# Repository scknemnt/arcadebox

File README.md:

# Arcade Box

Ev tipi ayakta kabin için **kiosk kabuk**. Windows veya Linux masaüstü görünmez: açılış → senin menün → oyun (RetroArch tam ekran) → menüye dönüş.

Bu depo **yazılımı** içerir. Ticari ROM, BIOS ve kutu görselleri **yok**. Kendi yasal dump’larını `roms/` ve `bios/` altına koyarsın.

**Hedef donanım:** Raspberry Pi 4 (8 GB) + HDMI (CRT/SCART sonra). Geliştirme: Windows.

---

## Ne yapar

- 4:3 CRT tarzı frontend (scanline, RGB mask, yıldız alanı)
- Klasör taraması: `roms/<sistem>/` içindeki her dosya menüde görünür
- Tek emülatör: **RetroArch** + libretro core
- Oyun çıkınca menü müziği ve liste geri gelir
- Servis menüsü: **F2** / logo (TEST, tuş ata, CRT)

Sistemler: Atari 2600, NES, SNES, Mega Drive, Arcade (FBNeo), Neo Geo, PlayStation.

---

## Bu repoda olmayanlar

| Klasör | Sen koyarsın |
|---|---|
| `roms/<sistem>/` | Yasal ROM / CHD / cue |
| `bios/psx/` | PS1 BIOS (`.bin`) |
| `roms/neogeo/neogeo.zip` | Neo Geo BIOS |
| `emulators/retroarch/` | Windows’ta portable RetroArch + `.dll` core |
| `music/` | İsteğe bağlı menü MP3 |

---

## Windows (geliştirme)

Python 3 (stdlib yeter). RetroArch portable:

```
emulators/retroarch/retroarch.exe
emulators/retroarch/cores/*.dll
```

| | |
|---|---|
| Pencere | `start.bat` |
| Tam ekran kiosk | `start-kiosk.bat` |
| Windows otostart | `kiosk/windows-otostart-kur.bat` bir kez |

Kabinde otomatik oturum aç (`netplwiz`). CRT için 800×600.

**Core’lar (Windows `.dll`):** Stella, Mesen (yedek Nestopia/FCEUmm), Snes9x, Genesis Plus GX, FBNeo, SwanStation (yedek Beetle PSX / PCSX ReARMed).

---

## Raspberry Pi 4 (kiosk)

- OS: **Raspberry Pi OS Lite 64-bit** (SD)
- Oyunlar: USB flash, klasör adı `ArcadeBox` (FAT32)
- Imager kullanıcı/hostname: `arcadebox`

USB’yi mavi USB3’e tak, SSH:

```sh
sudo mkdir -p /mnt/usb
sudo mount -t vfat /dev/sda1 /mnt/usb
cd /mnt/usb/ArcadeBox
tr -d '\r' < kiosk/pi-kur.sh > /tmp/pi-kur.sh
tr -d '\r' < kiosk/linux-start.sh > /tmp/linux-start.sh
sudo cp /tmp/linux-start.sh kiosk/linux-start.sh
sudo sh /tmp/pi-kur.sh
```

Windows satır sonları (`CRLF`) scripti bozar; `tr` ile LF yap. Script `ROOT=/` basarsa USB’den değil `/tmp` üzerinden çalışıyorsundur — normal. Autostart’ı README’deki Pi notlarına göre `~/.xinitrc` ile düzelt.

Core’lar (Linux `.so`, Windows DLL değil):

```sh
sudo apt-get install -y unzip wget
mkdir -p ~/.config/retroarch/cores
cd /tmp
for c in stella_libretro nestopia_libretro fceumm_libretro snes9x_libretro genesis_plus_gx_libretro fbneo_libretro pcsx_rearmed_libretro; do
  wget -O "$c.so.zip" "https://buildbot.libretro.com/nightly/linux/aarch64/latest/${c}.so.zip"
  unzip -o "$c.so.zip" -d ~/.config/retroarch/cores
done
```

veya `sh kiosk/pi-cores.sh`.

USB etiketi `ESD-USB` ise her açılışta `/mnt/arcade` bağlanır (`pi-kur.sh` fstab yazar). HDMI: güç soketine en yakın port.

---

## Klasörler

```
ArcadeBox/
  backend/arcadebox.py    yerel sunucu + RetroArch başlatıcı
  frontend/               kiosk UI
  data/                   sistem ve başlık eşlemesi (ROM yok)
  kiosk/                  Windows / Linux / Pi otostart
  roms/<sistem>/          senin dump’ların
  bios/                   senin BIOS’un
  config.json             port, tuşlar, CRT
```

Menü ROM dosya adından üretilir; arcade kısa adları `data/arcade-titles.json` ile çözülür.

Kapak indir (opsiyonel, libretro thumbnail CDN):

```
python backend/fetch_covers.py
```

---

## Kontroller

Çubuk / D-pad, **Gamepad0** tamam, **Gamepad1** geri, **Gamepad8** servis. Klavye: oklar, Enter, Esc, F2. PS3 pad USB HID olarak görünürse menüde çalışır; oyunda RetroArch bind.

---

## Lisans / yasal

Kod bu depoda. **ROM, BIOS ve ticari müzik dağıtılmaz.** Kendi kopyalarını kullan.

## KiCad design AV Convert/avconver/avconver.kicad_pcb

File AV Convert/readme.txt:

TV'ye VGA'den görüntüyü bu aparat ile aktarmak istiyorsanız PC'nizin çözünürlüğünü PAL görüntü verecek bir seviyey düşürmeniz lazım (örn. 640x480i). Bu çözünürlüğü de interlaced formatta göndermeniz gerekli. Yani PC'deki 640x480 çözünürlük  progressive'dir.

Tüm bunları sağlamak için de Soft15Khz denilen yazılım ile PC'nizin çözünürlüklerini modifiye etmeniz lazım.

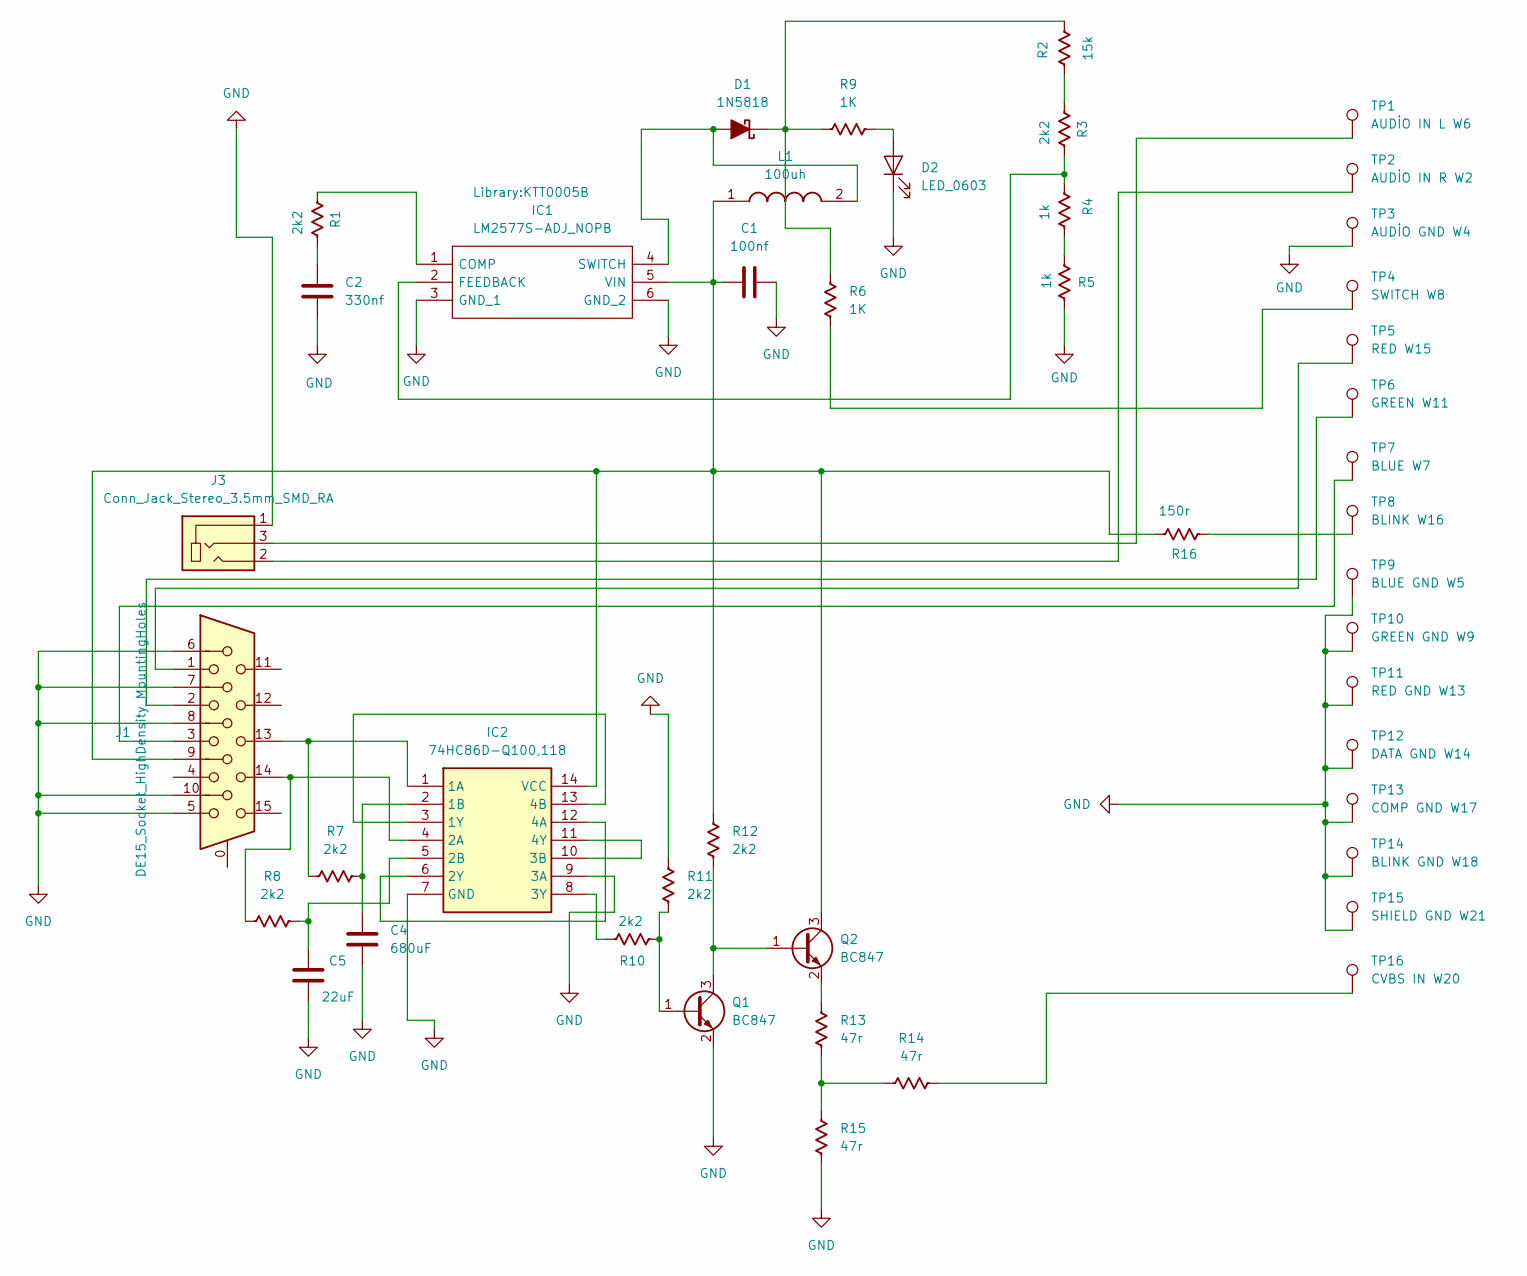
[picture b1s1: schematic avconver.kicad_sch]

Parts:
C1: 100nf; C_0603_1608Metric
C2: 330nf; C_0603_1608Metric
C4: 680uF; C_0603_1608Metric
C5: 22uF; C_0603_1608Metric
D1: 1N5818; D_SMA
D2: LED_0603
IC1: LM2577S-ADJ_NOPB; KTT0005B; Mouser Part Number 926-LM2577S-ADJ/NOPB
IC2: 74HC86D-Q100,118; 74HC86D-Q; Mouser Part Number 771-74HC86D-Q100118
J1: DE15_Socket_HighDensity_MountingHoles; DSUB-15-HD_Socket_Horizontal_P2.29x1.90mm_EdgePinOffset3.03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
J3: Conn_Jack_Stereo_3.5mm_SMD_RA; Conn_Jack_Stereo_3.5mm_CUI_SJ-3523-SMT-TR
L1: 100uh; 100UH; Mouser Part Number 994-MSS1583-104KED
Q1, Q2: BC847; SOT-23
R1, R3, R7, R8, R10, R11, R12: 2k2; R_0201_0603Metric
R2: 15k; R_0201_0603Metric
R4, R5: 1k; R_0201_0603Metric
R6, R9: 1K; R_0201_0603Metric
R13, R14, R15: 47r; R_0201_0603Metric
R16: 150r; R_0201_0603Metric
TP1: AUDİO IN L W6; TestPoint_Loop_D2.54mm_Drill1.5mm_Beaded
TP2: AUDİO IN R W2; TestPoint_Loop_D2.54mm_Drill1.5mm_Beaded
TP3: AUDİO GND W4; TestPoint_Loop_D2.54mm_Drill1.5mm_Beaded
TP4: SWITCH W8; TestPoint_Loop_D2.54mm_Drill1.5mm_Beaded
TP5: RED W15; TestPoint_Loop_D2.54mm_Drill1.5mm_Beaded
TP6: GREEN W11; TestPoint_Loop_D2.54mm_Drill1.5mm_Beaded
TP7: BLUE W7; TestPoint_Loop_D2.54mm_Drill1.5mm_Beaded
TP8: BLINK W16; TestPoint_Loop_D2.54mm_Drill1.5mm_Beaded
TP9: BLUE GND W5; TestPoint_Loop_D2.54mm_Drill1.5mm_Beaded
TP10: GREEN GND W9; TestPoint_Loop_D2.54mm_Drill1.5mm_Beaded
TP11: RED GND W13; TestPoint_Loop_D2.54mm_Drill1.5mm_Beaded
TP12: DATA GND W14; TestPoint_Loop_D2.54mm_Drill1.5mm_Beaded
TP13: COMP GND W17; TestPoint_Loop_D2.54mm_Drill1.5mm_Beaded
TP14: BLINK GND W18; TestPoint_Loop_D2.54mm_Drill1.5mm_Beaded
TP15: SHIELD GND W21; TestPoint_Loop_D2.54mm_Drill1.5mm_Beaded
TP16: CVBS IN W20; TestPoint_Loop_D2.54mm_Drill1.5mm_Beaded

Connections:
GND: C1.2, C2.2, C4.2, C5.2, D2.1 (K), IC1.3 (GND_1), IC1.6 (GND_2), IC2.7 (GND), IC2.9 (3A), J1.5, J1.6, J1.7, J1.8, J1.10, J3.1, Q1.2 (E), R5.2, R11.1, R15.2, TP3.1, TP9.1, TP10.1, TP11.1, TP12.1, TP13.1, TP14.1, TP15.1
unnamed: C2.1, R1.1
unnamed: D1.2 (A), IC1.4 (SWITCH), L1.2
unnamed: D1.1 (K), R2.1, R6.2, R9.1
unnamed: D2.2 (A), R9.2
unnamed: IC1.1 (COMP), R1.2
unnamed: IC1.2 (FEEDBACK), R3.1, R4.2
unnamed: C1.1, IC1.5 (VIN), IC2.14 (VCC), J1.9, L1.1, Q2.3 (C), R12.1, R16.2
unnamed: IC2.1 (1A), J1.13, R7.2
unnamed: C4.1, IC2.2 (1B), R7.1
unnamed: IC2.3 (1Y), IC2.13 (4B)
unnamed: IC2.4 (2A), J1.14, R8.2
unnamed: C5.1, IC2.5 (2B), R8.1
unnamed: IC2.6 (2Y), IC2.12 (4A)
unnamed: IC2.10 (3B), IC2.11 (4Y)
unnamed: IC2.8 (3Y), R10.2
unnamed: J1.1, TP5.1
unnamed: J1.2, TP6.1
unnamed: J1.3, TP7.1
unnamed: J3.2, TP2.1
unnamed: J3.3, TP1.1
unnamed: Q1.1 (B), R10.1, R11.2
unnamed: Q1.3 (C), Q2.1 (B), R12.2
unnamed: Q2.2 (E), R13.1
unnamed: R2.2, R3.2
unnamed: R4.1, R5.1
unnamed: R6.1, TP4.1
unnamed: R13.2, R14.1, R15.1
unnamed: R14.2, TP16.1
unnamed: R16.1, TP8.1

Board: 2 copper layers, 45 parts (0 on the bottom side), 30 nets, no tracks yet.
